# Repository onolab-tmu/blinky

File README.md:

Blinky Hardware
===============

> **Blinky**
>
> Blinkies are small electronic devices that make very bright light (usually flashing) light using LEDs and small batteries.
>
> -- Wikipedia

The **Blinky** is a sound-to-light conversion device. When many blinkies are used together, it becomes possible to do large scale
audio array processing by acquiring the light from all devices simultaneously with a camera. We described the devices and a couple
of applications in a [paper](http://www.apsipa.org/proceedings/2018/pdfs/0001899.pdf). Applications are, for example

* Monitoring 
* Speech enhancement
* Sound source localization in very large and challenging environment
* Blind Source Separation [arxiv](https://arxiv.org/abs/1904.02334)

Hardware
--------

The hardware is based on the ESP32 with a custom extension PCB bearing two MEMS
microphones and a few LEDs.
Details and necessary files are provided in the `hardware` folder.

Firmwares
---------

The folder `firmware` contains three different firmwares for the device.

### Blinky OTA Firmware

This is our working firmware that we have used for the device in our experiments.
It allows to do OTA updates and uses the DIP switch. This firmware reads sound
samples from the left microphone, compute the power for frames of 4 ms and apply
a non-linear transformation to map the value to the PWM range of the LED.
A few of the modes are for calibration only and just sweep the PWM duty cycles of the LED.

#### Quick Start

This section explains how to get the firmware running in a few commands.
For more detailed instructions, including over-the-air (OTA) updates, 
see `firmware/blinky_ota/README.md`.

1. Install the ESP-IDF by following the official instructions
    ([stable](https://docs.espressif.com/projects/esp-idf/en/stable/get-started/index.html))
    ([latest](https://docs.espressif.com/projects/esp-idf/en/latest/get-started/index.html)).
    In case it the first time working with the ESP32, it is recommended to try
    out a few example projects to learn how to compile and upload firmware to
    the device.

2. Build the firmware.

        cd firmware/blinky_ota/firmware
        
        # configure
        #  - serial port
        #  - device number
        #  - wireless network
        make menuconfig
        
        # compile and upload to device
        make flash

### Recorder Firmware

This firmware turns the device into a wireless stereo microphone.
The instructions to use this firmware are in `firmware/recorder/BlinkyRecorder_REAMDE_jp.pdf` (japanese only for now).

### Blank Firmware

This firmware is a stripped down version of the regular Blinky firmware. Its role
is to highlight how to read samples from one or both microphones and control the LEDs.

Software
--------

The `python` folder contains the `blinkytools` python package. This package
offers a graphical user interface (GUI) to easily capture the signals from
multiple Blinkies using a video camera, or from a pre-recorded video.

The package can be install from [pypi](https://pypi.org/project/blinkytools/) directly.

    pip install blinkytools

Authors
-------

* The board was designed by [Evixar](https://www.evixar.com/) under directions from Robin Scheibler.
* The code was written by Robin Scheibler and [Evixar](https://www.evixar.com/).

License
-------

MIT License for all the software, see `LICENSE.

CC-BY-SA 4.0 for the hardware.

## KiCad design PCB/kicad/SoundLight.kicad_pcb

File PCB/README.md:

Hardware CAD Files
==================

This folder contains the following.

* Kicad project files in the `kicad` folder.
* Illustration of the PCB from the bottom in `pcb.pdf`.
* Illustration of the PCB together with the location of holes in `pcb_and_holes.pdf`.
* CAD drawings of the enclosure and the holes drilled in it in `tw5-4-7_marking_top.pdf`.

The hardware is released under [CC-BY-SA 4.0](https://creativecommons.org/licenses/by-sa/4.0/) license.

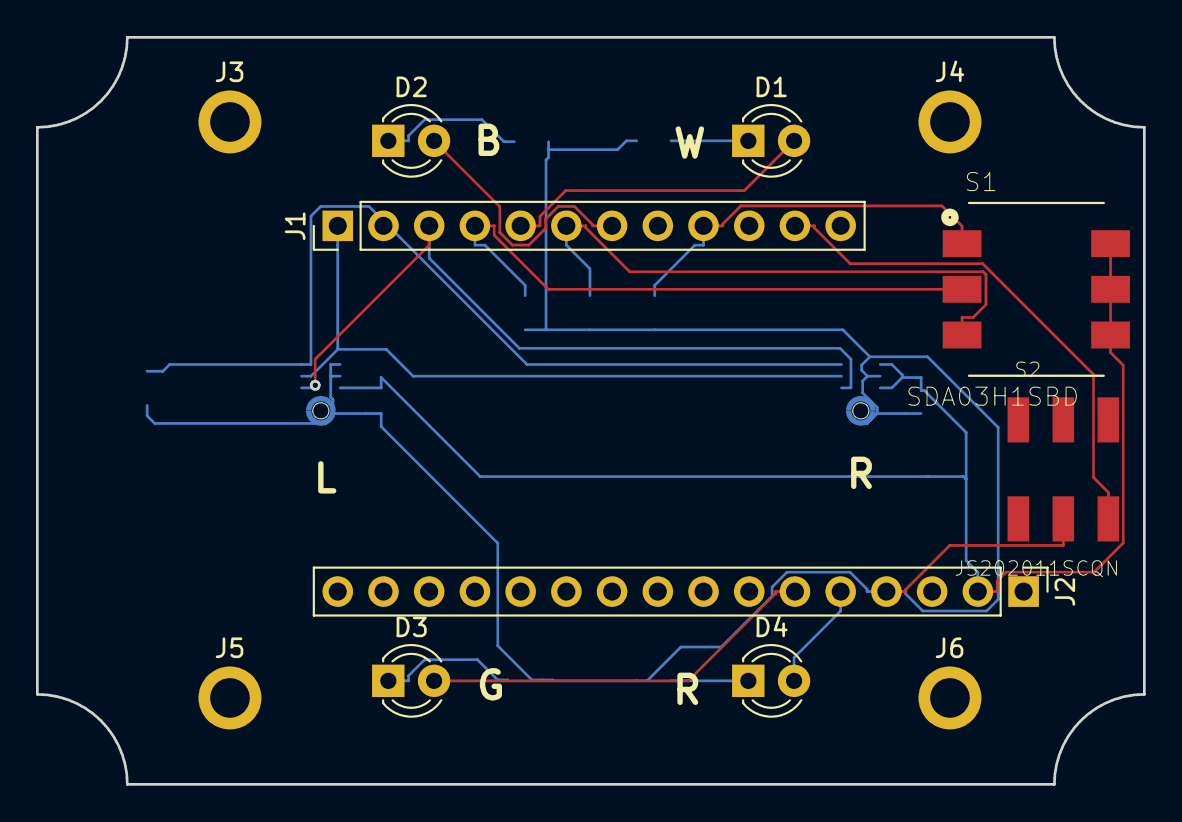
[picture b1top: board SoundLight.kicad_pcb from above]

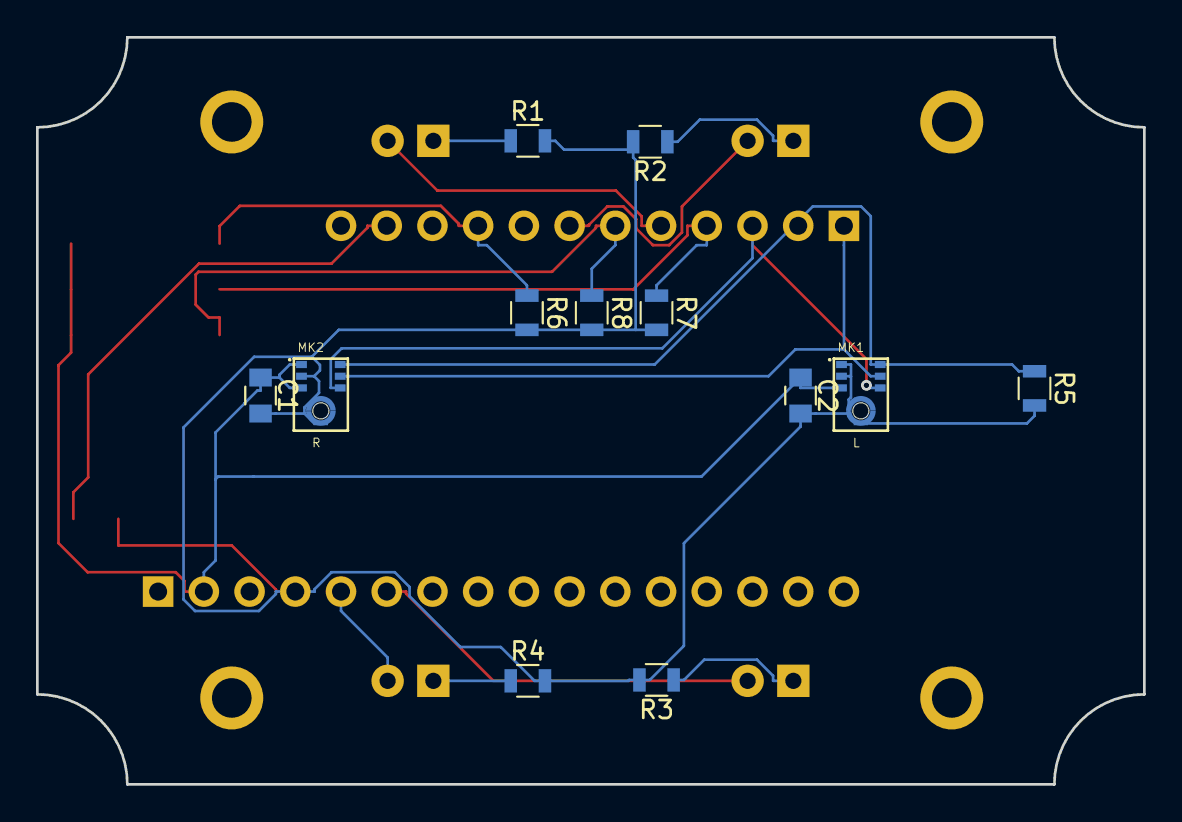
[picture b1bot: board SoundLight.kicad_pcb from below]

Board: 2 copper layers, 61.5 x 41.5 mm, 24 parts (12 on the bottom side), 17 nets.

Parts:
C1, C2: 0.1u; C_0805
D1: W; LED_D3.0mm
D2: B; LED_D3.0mm
D3: G; LED_D3.0mm
D4: R; LED_D3.0mm
J1: Conn_01x12; Pin_Header_Straight_1x12_Pitch2.54mm
J2: Conn_01x16; Pin_Header_Straight_1x16_Pitch2.54mm
J3, J4, J5, J6: Conn_01x01; MountingHole_2.2mm_M2_ISO7380_Pad
MK1: L; MIC_ICS-43432
MK2: R; MIC_ICS-43432
R1, R3: 100; R_0805
R2: 75; R_0805
R4: 180; R_0805
R5, R6, R7, R8: 100k; R_0805
S1: SDA03H1SBD; SW_SDA03H1SBD
S2: JS202011SCQN; SW_JS202011SCQN

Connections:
+3V3: C1.1, C2.1, J2.2, MK1.3, MK2.1, MK2.3, S1.2, S1.4, S1.6
/13: J1.9, R6.1, S1.1
/14: J1.3, MK1.5, MK2.5
/15: D1.2, J1.5
/27: D2.2, J1.7
/32: J1.4, R7.1, S1.3
/33: J1.6, R8.1, S1.5
/A0/26: D4.2, J2.5
/A1/25: D3.2, J2.6
/EN: J1.11, S2.3
/SCL/22: J1.2, MK1.7, MK2.7, R5.1
/SDA/23: J1.1, MK1.6, MK2.6
GND: C1.2, C2.2, J2.4, MK1.1, MK1.2, MK1.4, MK2.2, MK2.4, R1.2, R2.2, R3.2, R4.2, R5.2, R6.2, R7.2, R8.2, S2.2
unnamed: D1.1, R1.1
unnamed: D2.1, R2.1
unnamed: D3.1, R3.1
unnamed: D4.1, R4.1

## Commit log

2018-04-26 LED calibration firmware
2018-04-26 Added main firmware
2018-04-26 Added a few schematics.
2018-05-09 In LED calibration, turning on one LED at a time.
2018-05-11 Trying direct domain
2018-05-11 Updated non-linear function with speech and camera corrected
2018-05-18 Only one parameter for camera func
2018-05-18 Added script to flash multiple devices at once
2018-07-05 Added the dip switch read to the main code.
2018-07-05 change to LED calib
2018-07-26 Update README. Adds License file.
2018-07-26 small README update
2018-09-21 added the OTA code from Evixar
2018-11-08 OTA code for blinky
2018-11-08 README OTA
2018-11-28 Add white LED mode
2018-12-10 Low pass filters and new non-linear function
2019-06-07 back to APSIPA mapping
2019-06-07 Reorganizes Blinky-OTA folder
2019-06-07 Reorganizes different firmwares to be all in the firmware folder
2019-06-07 Starts improving README
2019-06-07 Partial translation of OTA README
2019-06-07 First version of microserver for easy firmware update
2019-06-10 Fixes bug in firmware that would write hash of new firmware even if download/install of new firmware fails.
2019-06-10 Fixes microserver. Now seemingly working.
2019-06-11 adds sdkconfig file for blinky_ota
2019-06-11 Adds the wireless recorder code
2019-06-21 Added the file necessary for menuconfig of blinky_ota
2019-06-21 Adds simple blank example
2019-06-21 Comment in blank/main/otohikari
2019-06-25 Corrects sample firmware
2019-07-12 Fixing duty_ref duty_max
2019-07-25 Fixed reference duty cycle in blinky ota firmware
2019-07-26 Translation of blinky_ota/REAMDE to english. Adds README for microserver
2019-07-26 Adds future import for recorder/client.py
2019-07-26 README filename to all caps
2019-07-26 Adds the kicad files
2019-07-26 Adds README for hardware
2019-07-26 Main README
2019-07-26 Removes unused files
2019-07-26 READMEs
2019-07-26 blinky ota README
2019-12-11 better filter
2019-12-13 Adds a GUI to check pixel values and inspect videos in real-time and on files
2019-12-17 Reorganize canvas in GUI
2019-12-19 More options in GUI
2019-12-19 Added viewer for Blinky files
2019-12-19 Now can save file with blinky signals
2019-12-24 1st attempt at relative sizing
2019-12-24 added industrial camera option
2019-12-26 Cleaned the Blinky firmware
2019-12-26 viewer size modification
2019-12-26 Cleaned up blinky firmware
2019-12-26 modularize gui
2020-01-06 Adds non-linearity in python package import
2020-01-07 python viewer video looping
2020-01-30 Better balance in the GUI
2020-01-30 Missing fiels in viewer
2020-01-30 Slightly more compact gui
2020-02-04 Moved python package to subdir, added license and README
2020-02-04 Renamed the package to blinkytools. Added some scripts for easier use
2020-02-04 More info in README
2020-02-04 PCB/ -> hardware/, README
2020-02-06 Adds the missing pillow to the package dependencies
2020-02-18 Fixes the FPS in blinky files
2021-02-22 removed old firmwares
2021-02-22 added new blinky_ota
2021-02-22 moved readme
2021-02-23 removed component.mk
2021-02-23 new branch
2021-06-08 added tiny-dnn
2021-06-08 update blinky_ota
2021-06-15 fix: fixed bug
